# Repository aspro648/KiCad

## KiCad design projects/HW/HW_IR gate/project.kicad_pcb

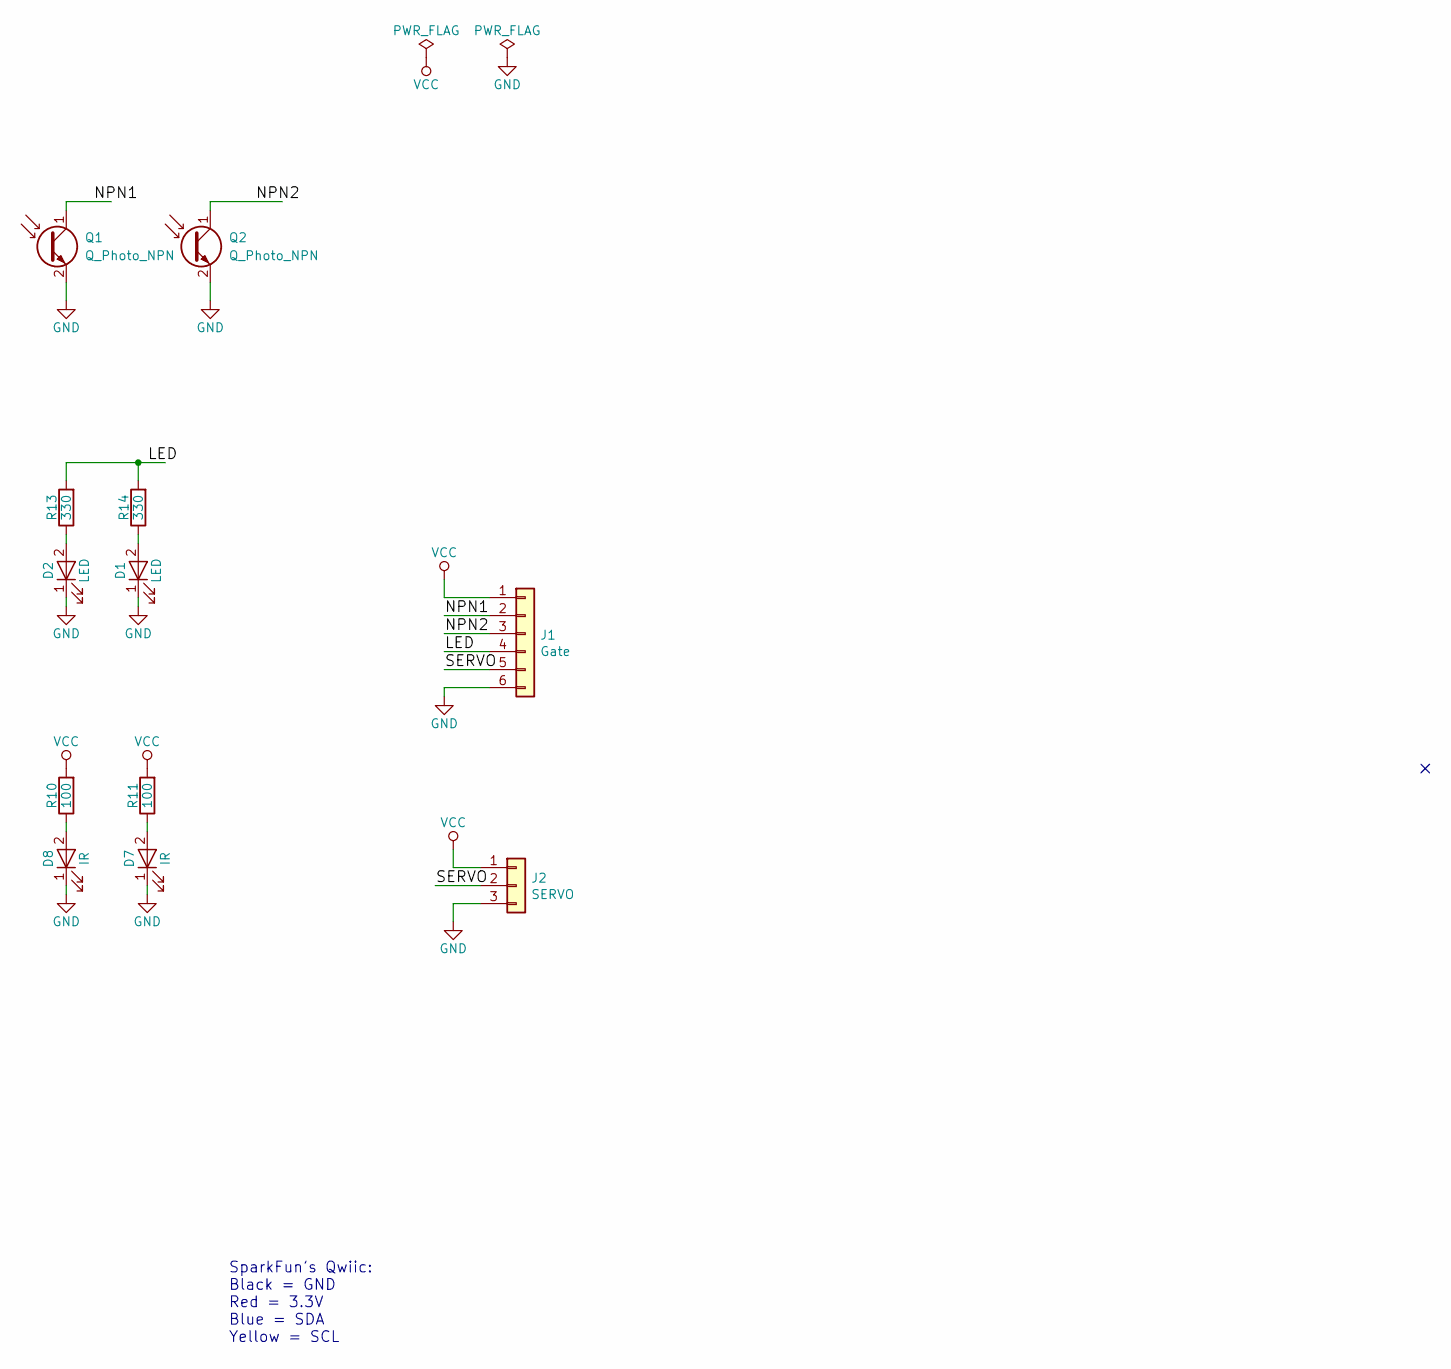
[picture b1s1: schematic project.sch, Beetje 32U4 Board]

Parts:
D1, D2: LED; LED_D3.0mm
D7, D8: IR; LED_D3.0mm
J1: Gate; Molex_PicoBlade_53048-0610_1x06_P1.25mm_Horizontal
J2: SERVO; PinHeader_1x03_P2.54mm_Vertical
Q1, Q2: Q_Photo_NPN; PHOTOTRANS
R10, R11: 100; R_0805_2012Metric
R13, R14: 330; R_0805_2012Metric

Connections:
/LED: J1.4, R13.2, R14.2
/NPN1: J1.2, Q1.1 (C)
/NPN2: J1.3, Q2.1 (C)
/SERVO: J1.5, J2.2
GND: D1.1 (K), D2.1 (K), D7.1 (K), D8.1 (K), J1.6, J2.3, Q1.2 (E), Q2.2 (E)
unnamed: D1.2 (A), R14.1
unnamed: D2.2 (A), R13.1
unnamed: D7.2 (A), R11.1
unnamed: D8.2 (A), R10.1
VCC: J1.1, J2.1, R10.2, R11.2

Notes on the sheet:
SparkFun's Qwiic: Black = GND Red = 3.3V Blue = SDA Yellow = SCL

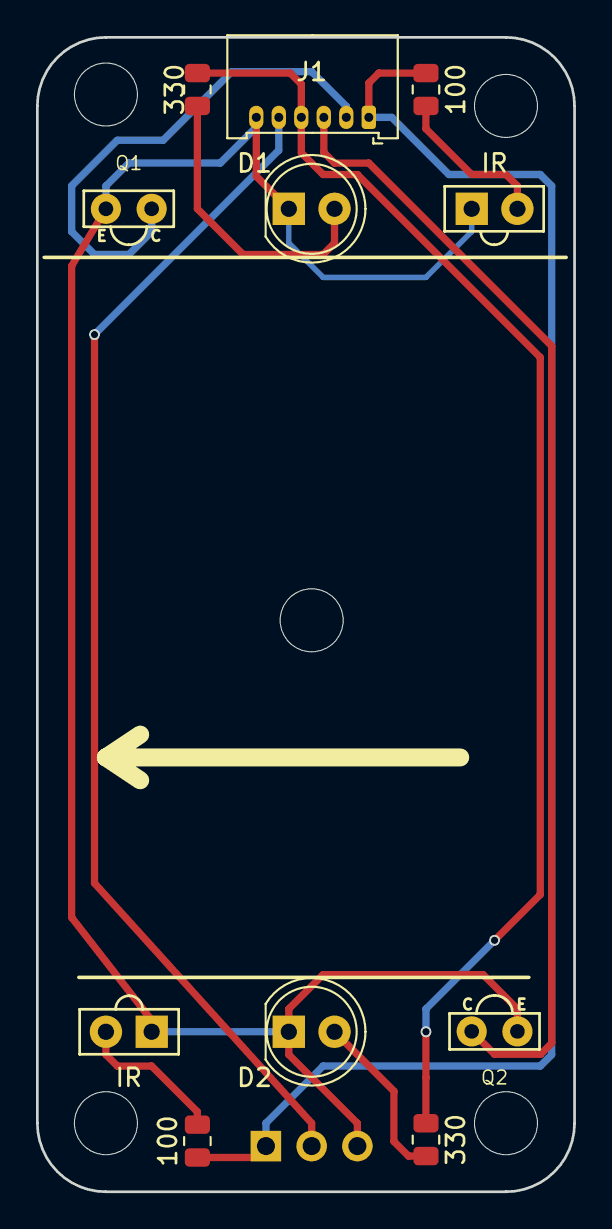
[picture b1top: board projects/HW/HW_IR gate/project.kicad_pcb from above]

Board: 2 copper layers, 29.8 x 64.1 mm, 13 parts (1 on the bottom side), 10 nets.

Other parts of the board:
VAL: MadeInOregonRev25

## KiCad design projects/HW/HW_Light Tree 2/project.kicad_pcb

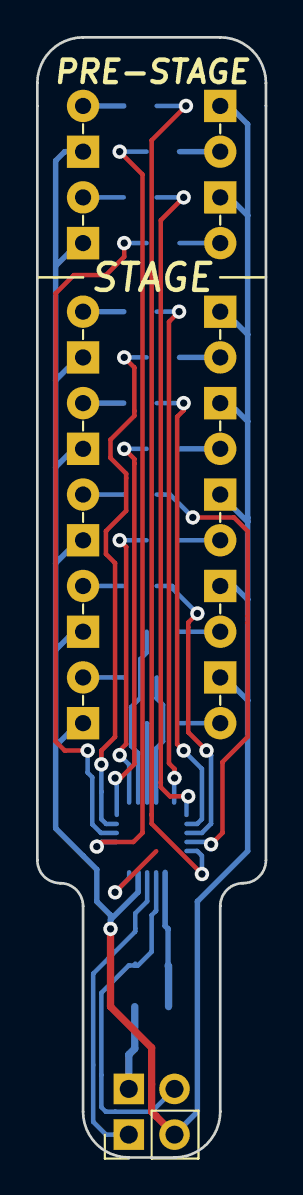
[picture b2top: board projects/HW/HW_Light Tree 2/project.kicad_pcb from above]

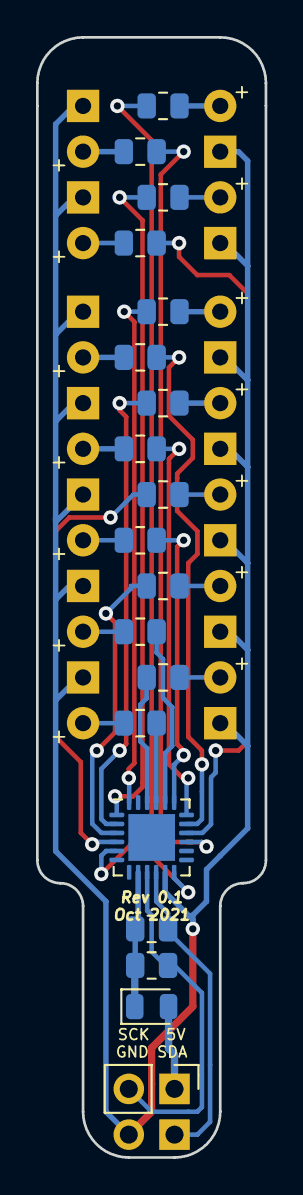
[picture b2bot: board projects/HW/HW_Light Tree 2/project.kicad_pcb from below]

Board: 2 copper layers, 12.7 x 62.2 mm, 34 parts (19 on the bottom side), 33 nets.

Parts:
D1, D2, D3, D4, D5, D6, D7, D8, D9, D10, D11, D12, D13, D14: LED; LED_D3.0mm
D15: D; D_0805_2012Metric
J1, J2: I2C; PinHeader_1x02_P2.54mm_Vertical
R1, R2, R3, R4, R5, R6, R7, R8, R9, R10, R11, R12, R13, R14: 330; R_0805_2012Metric
R15, R16: 4K7; R_0805_2012Metric
U1: MCP23018_ML; QFN-24-1EP_4x4mm_P0.5mm_EP2.6x2.6mm

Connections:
+5V: D15.1, R15.1, R16.1, U1.8, U1.12
/GP0: R5.1, U1.24
/GP1: R3.1, U1.1
/GP2: R7.1, U1.2
/GP3: R11.1, U1.3
/GP4: R9.1, U1.4
/GP5: R1.1, U1.5
/GP8: R2.1, U1.15
/GP9: R4.1, U1.16
/GP10: R6.1, U1.17
/GP11: R8.1, U1.18
/GP12: R10.1, U1.19
/GP13: R12.1, U1.20
/GP14: R14.1, U1.21
/GP15: R13.1, U1.22
/SCK: J1.2, R16.2, U1.9
/SDA: J2.1, R15.2, U1.10
GND: D1.1, D2.1, D3.1, D4.1, D5.1, D6.1, D7.1, D8.1, D9.1, D10.1, D11.1, D12.1, D13.1, D14.1, J2.2, U1.11, U1.23
unnamed: D1.2, R1.2
unnamed: D2.2, R2.2
unnamed: D3.2, R3.2
unnamed: D4.2, R4.2
unnamed: D5.2, R5.2
unnamed: D6.2, R6.2
unnamed: D7.2, R7.2
unnamed: D8.2, R8.2
unnamed: D9.2, R9.2
unnamed: D10.2, R10.2
unnamed: D11.2, R11.2
unnamed: D12.2, R12.2
unnamed: D13.2, R13.2
unnamed: D14.2, R14.2
unnamed: D15.2, J1.1

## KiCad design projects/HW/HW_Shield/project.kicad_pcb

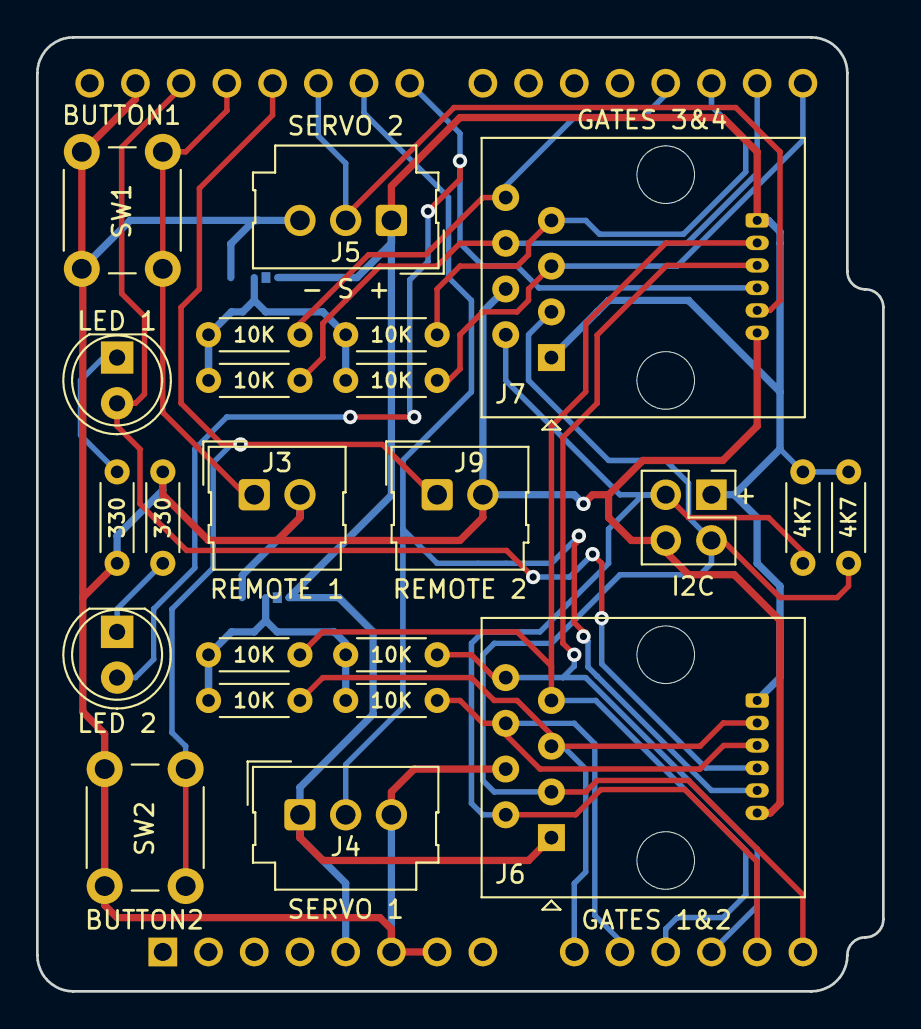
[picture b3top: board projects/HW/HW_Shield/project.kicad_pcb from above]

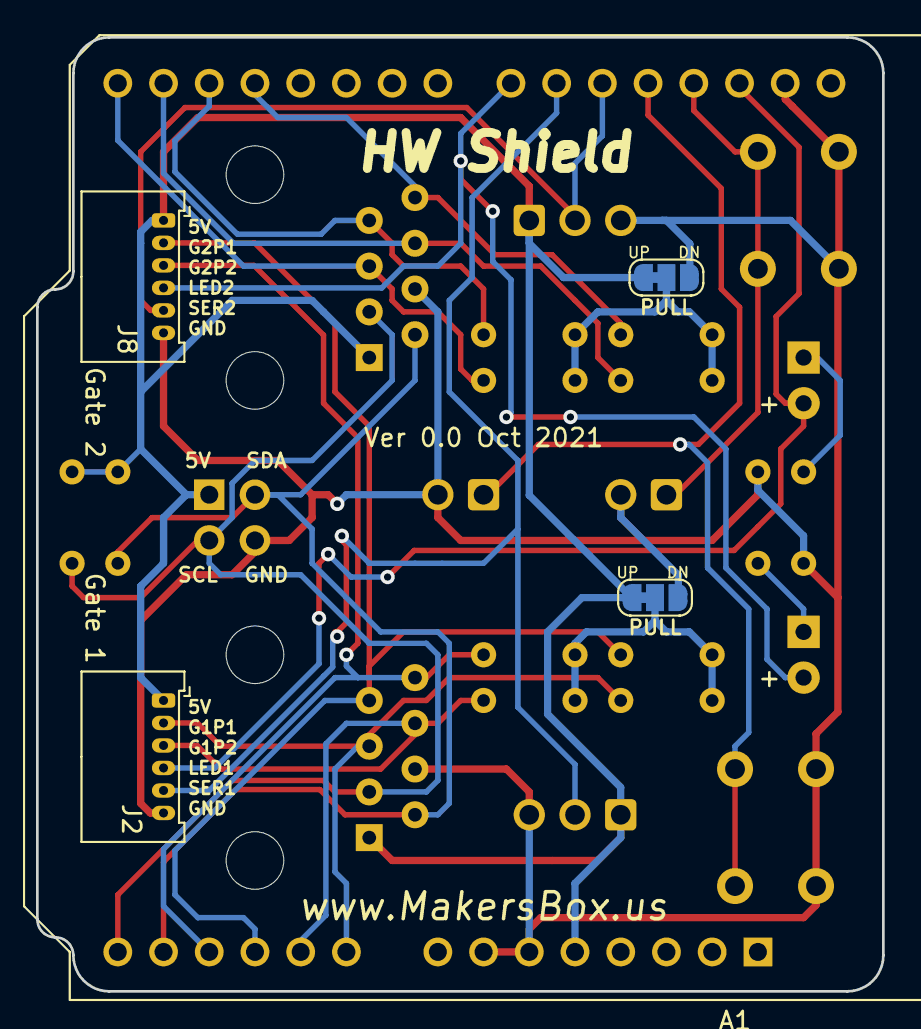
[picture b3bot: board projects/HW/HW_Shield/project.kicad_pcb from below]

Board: 2 copper layers, 47.0 x 53.0 mm, 28 parts (5 on the bottom side), 22 nets.

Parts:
A1: Arduino_UNO_R2
D1: LED 1; LED_D5.0mm
D2: LED 2; LED_D5.0mm
J1: I2C; PinSocket_2x02_P2.54mm_Vertical
J2: Gate 1; Molex_PicoBlade_53048-0610_1x06_P1.25mm_Horizontal
J3: REMOTE 1; Molex_SL_171971-0002_1x02_P2.54mm_Vertical
J4: SERVO 1; Molex_SL_171971-0003_1x03_P2.54mm_Vertical
J5: SERVO 2; Molex_SL_171971-0003_1x03_P2.54mm_Vertical
J6: GATES 1&2; RJ45_Amphenol_54602-x08_Horizontal
J7: GATES 3&4; RJ45_Amphenol_54602-x08_Horizontal
J8: Gate 2; Molex_PicoBlade_53048-0610_1x06_P1.25mm_Horizontal
J9: REMOTE 2; Molex_SL_171971-0002_1x02_P2.54mm_Vertical
JP1, JP2: PULL; SolderJumper-3_P1.3mm_Bridged12_RoundedPad1.0x1.5mm
R1, R2: 330; R_P5.08mm_Horizontal
R3, R4, R5, R6, R7, R8, R9, R10: 10K; R_P5.08mm_Horizontal
R11, R12: 4K7; R_P5.08mm_Horizontal
SW1: BUTTON1; SW_PUSH_6mm
SW2: BUTTON2; SW_PUSH_6mm

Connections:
+5V: A1.5, J1.1, J2.1, J4.1, J5.1, J6.1, J7.1, J8.1, JP1.1, JP2.1, R11.2, R12.2
/BUTTON1: A1.27, J3.1, SW1.1
/BUTTON2: A1.26, J9.1, SW2.1
/G1_P1: A1.9, J2.2, J6.5, R3.1
/G1_P2: A1.10, J2.3, J6.6, R4.1
/G2_P1: A1.11, J6.7, J8.2, R5.1
/G2_P2: A1.12, J6.8, J8.3, R6.1
/G3_P1: A1.15, J7.5, R7.1
/G3_P2: A1.16, J7.6, R8.1
/G4_P1: A1.17, J7.7, R9.1
/G4_P2: A1.18, J7.8, R10.1
/LED1: A1.28, D1.2, J2.4
/LED2: A1.23, D2.2, J8.4
/SCL: A1.14, J1.3, J6.3, J7.3, R12.1
/SDA: A1.13, J1.2, J6.2, J7.2, R11.1
/SERVO1: A1.24, J2.5, J4.2
/SERVO2: A1.25, J5.2, J8.5
GND: A1.6, A1.7, A1.29, J1.4, J2.6, J3.2, J4.3, J5.3, J6.4, J7.4, J8.6, J9.2, JP1.3, JP2.3, R1.2, R2.2, SW1.2, SW2.2
unnamed: D1.1, R1.1
unnamed: D2.1, R2.1
unnamed: JP1.2, R3.2, R4.2, R5.2, R6.2
unnamed: JP2.2, R7.2, R8.2, R9.2, R10.2

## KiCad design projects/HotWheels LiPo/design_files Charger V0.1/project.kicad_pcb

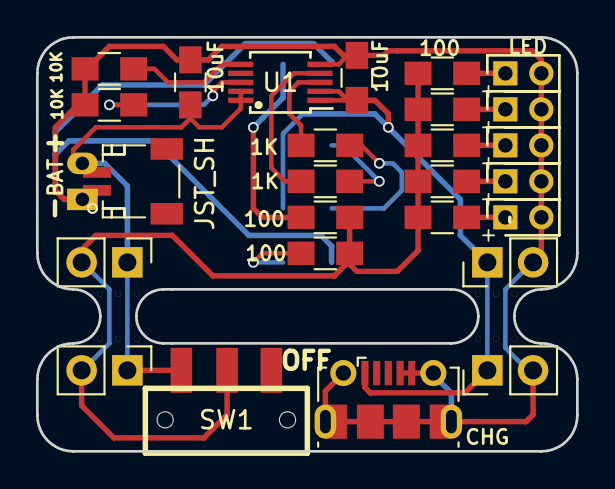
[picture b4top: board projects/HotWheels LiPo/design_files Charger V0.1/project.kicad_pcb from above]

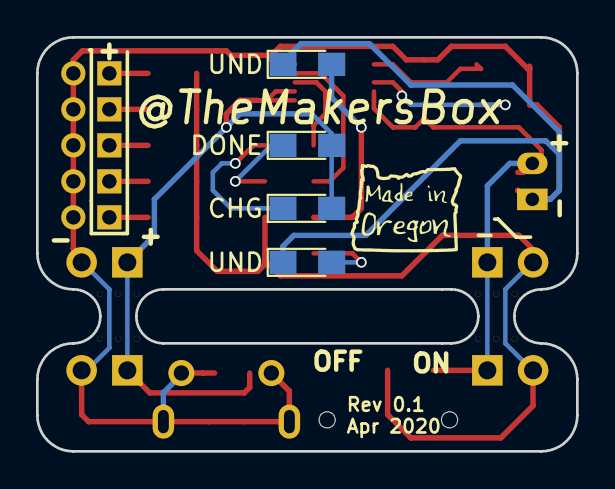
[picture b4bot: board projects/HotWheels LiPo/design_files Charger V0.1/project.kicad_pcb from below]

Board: 2 copper layers, 30.0 x 23.0 mm, 32 parts (4 on the bottom side), 17 nets.

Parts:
C1, C2: 10uF; C_0805_HandSoldering
D2: CHG; LED_0805_HandSoldering
D3: DONE; LED_0805_HandSoldering
D4, D5: UND; LED_0805_HandSoldering
J1, J6, J7, J8, J9: LED; PIN_HEADER_LED
J2: CHG; USB_Micro-B_Molex-105017-0001
J3: BAT; JST_SH_SM02B-SRSS-TB_02x1.00mm_Angled
J4, J5, J44, J55: CONN; Pin_Header_Straight_1x02_Pitch2.54mm
J10: JST_PH; JST_PH_S2B-PH-K_02x2.00mm_Angled
R2, R3: 1K; R_0805_HandSoldering
R4, R5: 10K; R_0805_HandSoldering
R6, R7, R8, R9, R10, R11, R12: 100; R_0805_HandSoldering
SW1: SW_SPDT; SPST_SMD
U1: MCP73833; MSOP-10_3x3mm_Pitch0.5mm
VAL: MadeInOregonRev25

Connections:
GND: C1.2, C2.2, D4.1, D5.1, J1.2, J2.4, J2.5, J3.1, J5.2, J6.2, J7.2, J8.2, J9.2, J10.1, J55.2, R4.2, R5.2, U1.5
unnamed: C2.1, J3.2, J4.1, J10.2, J44.1, SW1.1, U1.9, U1.10
unnamed: D2.1, R2.2
unnamed: D3.1, R3.2
unnamed: D4.2, R11.2
unnamed: D5.2, R12.2
unnamed: J1.1, R6.2
unnamed: J4.2, J44.2, R6.1, R7.1, R8.1, R9.1, R10.1, R11.1, R12.1, SW1.2
unnamed: J6.1, R7.2
unnamed: J7.1, R8.2
unnamed: J8.1, R9.2
unnamed: J9.1, R10.2
unnamed: R2.1, U1.3
unnamed: R3.1, U1.4
unnamed: R4.1, U1.8
unnamed: R5.1, U1.6
VBUS: C1.1, D2.2, D3.2, J2.1, J5.1, J55.1, U1.1, U1.2

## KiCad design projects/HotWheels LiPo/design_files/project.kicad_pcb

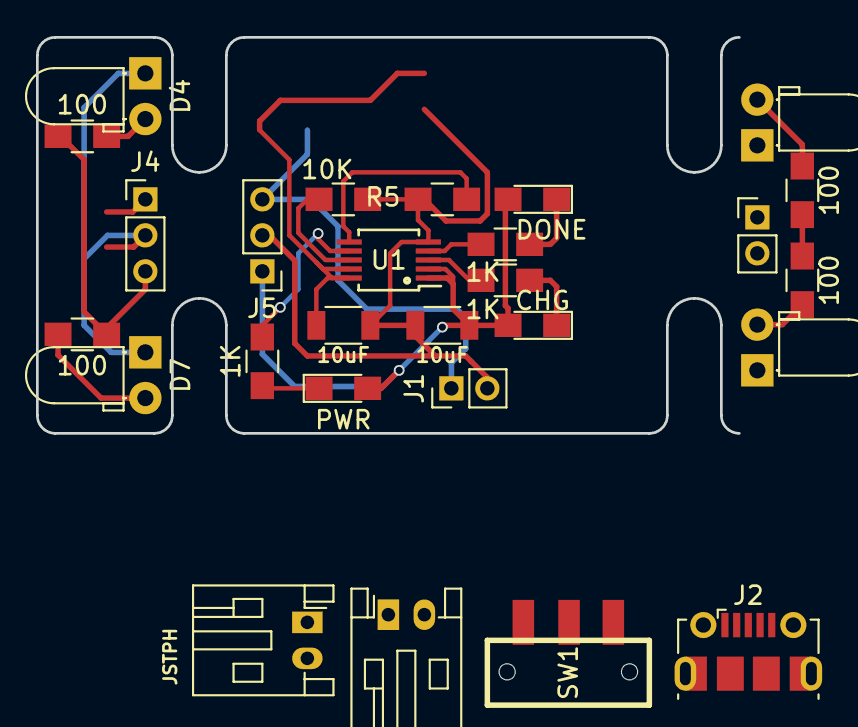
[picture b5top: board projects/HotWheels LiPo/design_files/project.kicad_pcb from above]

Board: 2 copper layers, 28 parts (0 on the bottom side), 21 nets.

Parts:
C1, C2: 10uF; C_1206
D1: PWR; LED_0805_HandSoldering
D2: CHG; LED_0805_HandSoldering
D3: DONE; LED_0805_HandSoldering
D4, D5, D6, D7: LED; LED_D3.0mm_Horizontal_O1.27mm_Z10.0mm
J1, J6: CON; Pin_Header_Straight_1x02_Pitch2.00mm
J2: USB_B; USB_Micro-B_Molex-105017-0001
J3, J3#2: JSTPH; JST_PH_S2B-PH-K_02x2.00mm_Angled
J4, J5: CONN; Pin_Header_Straight_1x03_Pitch2.00mm
R1, R2, R3: 1K; R_0805_HandSoldering
R4, R5: 10K; R_0805_HandSoldering
R6, R7, R8, R9: 100; R_0805_HandSoldering
SW1: SW_SPDT; SPST_SMD
U1: MCP73833; MSOP-10_3x3mm_Pitch0.5mm
VAL: MadeInOregonRev25

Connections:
/LED_PWR: J1.1, J5.3, SW1.2
GND: C1.2, C2.2, J1.2, J3.2, J3#2.2, J5.2, R4.2, R5.2, U1.5
unnamed: C2.1, J3.1, J3#2.1, SW1.3, U1.9, U1.10
unnamed: D1.1, R1.2
unnamed: D2.1, R2.2
unnamed: D3.1, R3.2
unnamed: D4.1, D7.1, J2.4, J2.5, J4.2
unnamed: D4.2, R6.1
unnamed: D5.1, D6.1, J6.2
unnamed: D5.2, R8.2
unnamed: D6.2, R9.2
unnamed: D7.2, R7.1
unnamed: J2.1, J4.1
unnamed: J4.3, R6.2, R7.2
unnamed: J6.1, R8.1, R9.1
unnamed: R1.1, U1.7
unnamed: R2.1, U1.3
unnamed: R3.1, U1.4
unnamed: R4.1, U1.8
unnamed: R5.1, U1.6
VBUS: C1.1, D1.2, D2.2, D3.2, J5.1, U1.1, U1.2

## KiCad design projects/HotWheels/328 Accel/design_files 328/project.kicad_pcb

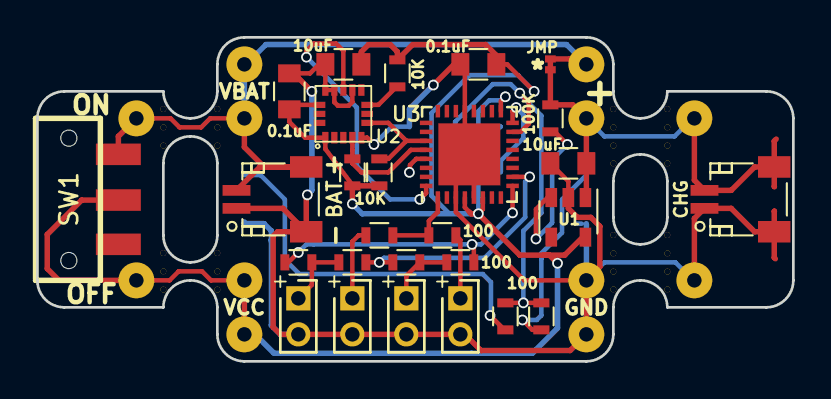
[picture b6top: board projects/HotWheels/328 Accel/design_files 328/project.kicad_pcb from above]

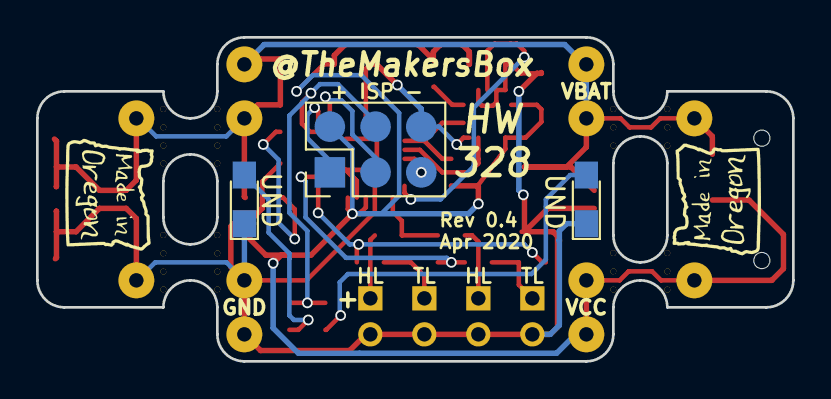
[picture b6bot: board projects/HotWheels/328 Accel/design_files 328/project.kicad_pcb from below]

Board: 2 copper layers, 42.0 x 18.0 mm, 44 parts (3 on the bottom side), 21 nets.

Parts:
C1, C4: 0.1uF; C_0805
C2, C3: 10uF; C_0805
CON1: AVR-ISP-6; Pin_Header_Straight_2x03_Pitch2.54mm
D4, D5: UND; LED_0805_HandSoldering
J1, J6: HL; PIN_HEADER_LED
J2: CHG; JST_SH_SM02B-SRSS-TB_02x1.00mm_Angled
J3: BAT; JST_SH_SM02B-SRSS-TB_02x1.00mm_Angled
J7, J8: TL; PIN_HEADER_LED
J44, J45, J46, J47, J48, J49, J54, J55, J56, J57, J58, J59: Conn; SolderWirePad_single_0-8mmDrill
JP1: JMP; Jumper
R1: 100K; R_0603
R2, R3, R4: 10K; R_0603
R5, R6, R7, R8, R9, R10, R11, R12: 100; R_0603
SW1: SW_SPDT; SPST_SMD
U1: MIC5225-3.3; SOT-23-5
U2: LIS3DH; LIS3DH_EP
U3: ATMEGA328-MU; QFN-32-1EP_5x5mm_Pitch0.5mm
VAL: MadeInOregonRev25
VAL#2: MadeInOregonRev25

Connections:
+BATT: C2.1, J2.2, J3.2, J44.1, J46.1, J48.1, J54.1, J56.1, J58.1, JP1.1, JP1.2, R1.1, SW1.1, U1.1
/D2: U2.11, U3.32
/D3: R6.1, R7.1, U3.1
/D5: R8.1, R9.1, U3.9
/D6: R5.1, R10.1, U3.10
/MISO: CON1.1, U3.16
/MOSI: CON1.4, R11.1, R12.1, U3.15
/RESET: CON1.5, U3.29
/SCK: CON1.3, U3.17
/SCL: R4.1, U2.4, U3.28
/SDA: R3.1, U2.6, U3.27
GND: C1.2, C2.2, C3.2, C4.2, CON1.6, D4.1, D5.1, J1.2, J2.1, J3.1, J6.2, J7.2, J8.2, J45.1, J47.1, J49.1, U1.2, U2.5, U2.10, U2.12, U2.13, U3.3, U3.5, U3.21
unnamed: D4.2, R11.2
unnamed: D5.2, R12.2
unnamed: J1.1, R6.2
unnamed: J6.1, R7.2
unnamed: J7.1, R5.2, R8.2
unnamed: J8.1, R9.2, R10.2
unnamed: R1.2, U1.3
unnamed: R2.1, U2.8
VCC: C1.1, C3.1, C4.1, CON1.2, J55.1, J57.1, J59.1, R2.2, R3.2, R4.2, SW1.2, U1.5, U2.1, U2.14, U3.4, U3.6
